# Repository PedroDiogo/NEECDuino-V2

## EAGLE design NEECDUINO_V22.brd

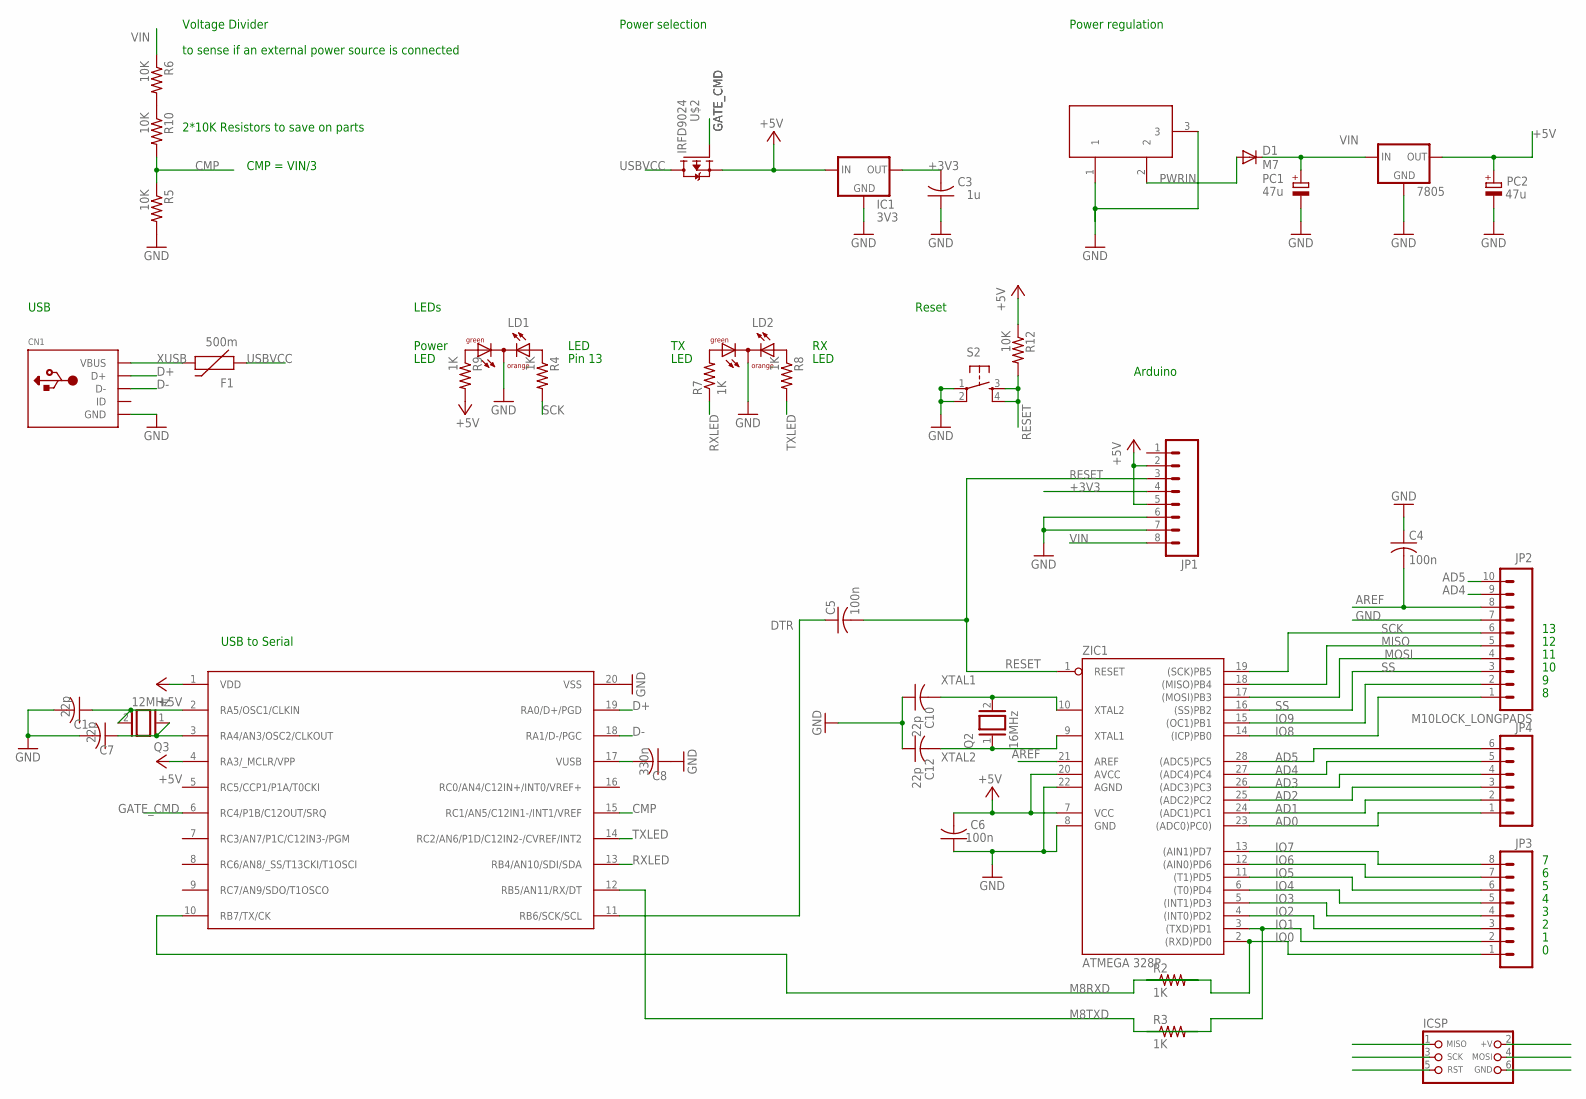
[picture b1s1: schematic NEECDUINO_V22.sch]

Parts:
7805: 78XXL
C1, C7, C10, C12: 22p; C025-025X050
C3: 1u; C050-024X044
C4, C5, C6: 100n; C025-025X050
C8: 330n; C025-025X050
CN1: USBMOLEX; USB-MINIB-THM-MOLEX
D1: M7; D-10
F1: 500m; PTC
IC1: 3V3; TO92-INLINE
ICSP: CON_HEADER_PRG_AVR_ICSP; HEADER_PRG_2X03
JP1, JP3: M08LOCK_LONGPADS; 1X08_LOCK_LONGPADS
JP2: M10LOCK_LONGPADS; 1X10_LOCK_LONGPADS
JP4: M06LOCK_LONGPADS; 1X06_LOCK_LONGPADS
LD1, LD2: DUOLED-GO-C; DUOLED-C-3MM
PC1, PC2: 47u; E2,5-5
Q2: 16MHz; QS
Q3: 12MHz; QS
R2, R3, R4, R7, R8, R9: 1K; 0204/5
R5, R6, R10, R12: 10K; 0204/5
S2: TAC_SWITCHPTH; TACTILE-PTH
U$1: PIC18F14K50; DIL20
U$2: IRFD9024; DIL04
X1: DC21MMX; DC-21MM
ZIC1: ATMEGA 328P; DIL28-3

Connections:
+3V3: C3.2, IC1.1 (OUT), JP1.4
+5V: 7805.OUT, C6.2, IC1.3 (IN), ICSP.2 (+V), JP1.2, JP1.5, PC2.+, R9.2, R12.1, U$1.1 (VDD), U$1.4 (RA3/_MCLR/VPP), U$2.4 (S), ZIC1.7 (VCC), ZIC1.20 (AVCC)
AD0: JP4.1, ZIC1.23 ((ADC0)PC0))
AD1: JP4.2, ZIC1.24 ((ADC1)PC1)
AD2: JP4.3, ZIC1.25 ((ADC2)PC2)
AD3: JP4.4, ZIC1.26 ((ADC3)PC3)
AD4: JP2.9, JP4.5, ZIC1.27 ((ADC4)PC4)
AD5: JP2.10, JP4.6, ZIC1.28 ((ADC5)PC5)
AREF: C4.2, JP2.8, ZIC1.21 (AREF)
CMP: R5.1, R10.2, U$1.15 (RC1/AN5/C12IN1-/INT1/VREF)
D+: CN1.D+, U$1.19 (RA0/D+/PGD)
D-: CN1.D-, U$1.18 (RA1/D-/PGC)
DTR: C5.1, U$1.11 (RB6/SCK/SCL)
GATE_CMD: U$1.6 (RC4/P1B/C12OUT/SRQ), U$2.3 (G)
GND: 7805.GND, C1.2, C3.1, C4.1, C6.1, C7.2, C8.1, C10.1, C12.1, CN1.GND, IC1.2 (GND), ICSP.6 (GND), JP1.6, JP1.7, JP2.7, LD1.C, LD2.C, PC1.-, PC2.-, R5.2, S2.1, S2.2, U$1.20 (VSS), X1.1, X1.3, ZIC1.8 (GND), ZIC1.22 (AGND)
IO0: JP3.1, R2.1, ZIC1.2 ((RXD)PD0)
IO1: JP3.2, R3.1, ZIC1.3 ((TXD)PD1)
IO2: JP3.3, ZIC1.4 ((INT0)PD2)
IO3: JP3.4, ZIC1.5 ((INT1)PD3)
IO4: JP3.5, ZIC1.6 ((T0)PD4)
IO5: JP3.6, ZIC1.11 ((T1)PD5)
IO6: JP3.7, ZIC1.12 ((AIN0)PD6)
IO7: JP3.8, ZIC1.13 ((AIN1)PD7)
IO8: JP2.1, ZIC1.14 ((ICP)PB0)
IO9: JP2.2, ZIC1.15 ((OC1)PB1)
M8RXD: R2.2, U$1.10 (RB7/TX/CK)
M8TXD: R3.2, U$1.12 (RB5/AN11/RX/DT)
MISO: ICSP.1 (MISO), JP2.5, ZIC1.18 ((MISO)PB4)
MOSI: ICSP.4 (MOSI), JP2.4, ZIC1.17 ((MOSI)PB3)
unnamed: R6.2, R10.1
unnamed: LD1.AX (AR), R9.1
unnamed: LD1.AR (AY), R4.1
unnamed: LD2.AX (AR), R7.2
unnamed: LD2.AR (AY), R8.1
unnamed: C7.1, Q3.1, U$1.3 (RA4/AN3/OSC2/CLKOUT)
unnamed: C1.1, Q3.2, U$1.2 (RA5/OSC1/CLKIN)
unnamed: C8.2, U$1.17 (VUSB)
PWRIN: D1.A, X1.2
RESET: C5.2, ICSP.5 (RST), JP1.3, R12.2, S2.3, S2.4, ZIC1.1 (RESET)
RXLED: R7.1, U$1.13 (RB4/AN10/SDI/SDA)
SCK: ICSP.3 (SCK), JP2.6, R4.2, ZIC1.19 ((SCK)PB5)
SS: JP2.3, ZIC1.16 ((SS)PB2)
TXLED: R8.2, U$1.14 (RC2/AN6/P1D/C12IN2-/CVREF/INT2)
USBVCC: F1.P$1 (1), U$2.1 (D), U$2.2 (D)
VIN: 7805.IN, D1.C, JP1.8, PC1.+, R6.1
XTAL1: C10.2, Q2.2, ZIC1.10 (XTAL2)
XTAL2: C12.2, Q2.1, ZIC1.9 (XTAL1)
XUSB: CN1.VBUS, F1.P$2 (2)

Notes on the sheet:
2*10K Resistors to save on parts
USB
Voltage Divider
to sense if an external power source is connected
Power selection
Power regulation
USB to Serial
Arduino
Reset
CMP = VIN/3
LEDs
Power
LED
Pin 13

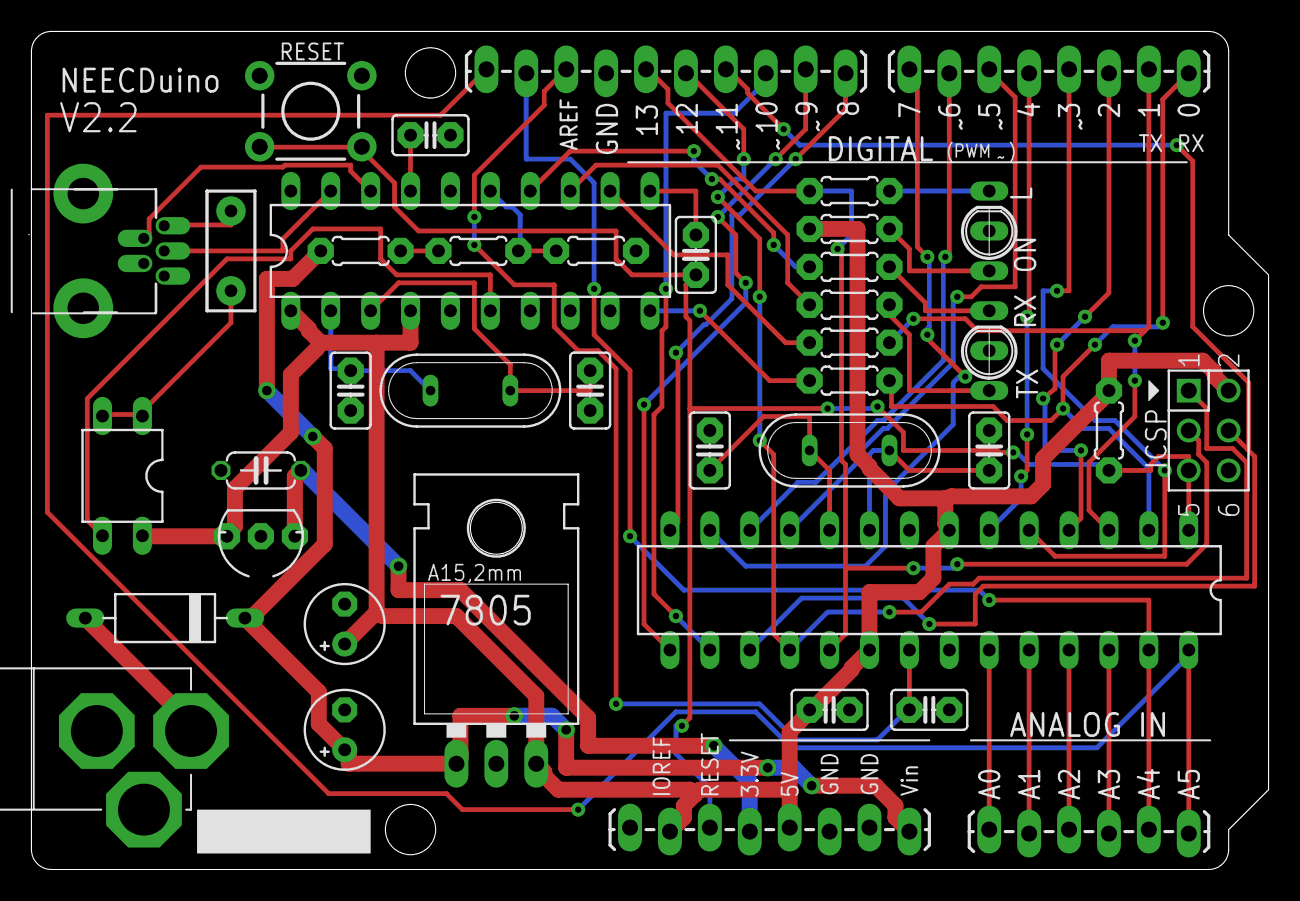
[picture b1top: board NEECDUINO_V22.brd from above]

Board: 2 copper layers, 78.7 x 53.3 mm, 40 parts (0 on the bottom side), 48 nets.

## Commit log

2012-05-02 Added Images
    Images of the board layout and routing and schematic were added to the
    project

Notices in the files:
parts and their libraries:
SparkFun: Licensing: CC v3.0 Share-Alike You are welcome to use this library for commercial purposes.
